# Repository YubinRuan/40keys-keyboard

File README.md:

# 40keys-keyboard
The PCB of 40keys-keyboard made by KICAD

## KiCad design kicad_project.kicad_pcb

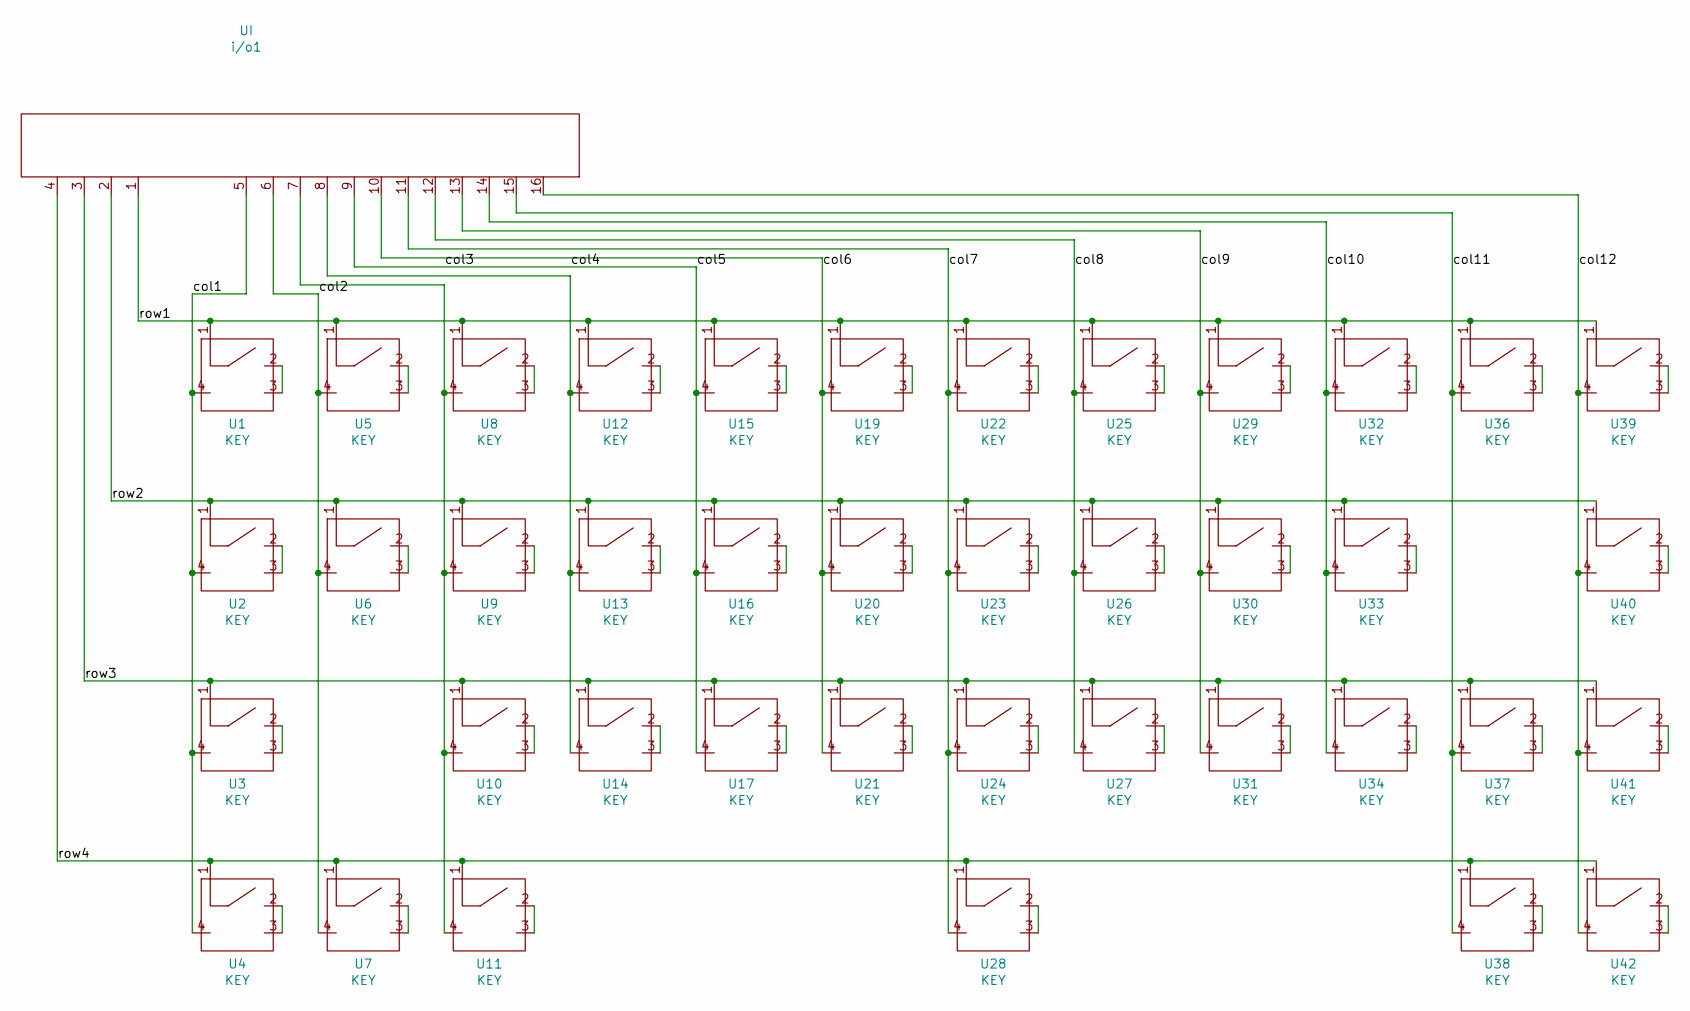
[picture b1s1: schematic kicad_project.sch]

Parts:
U1, U2, U3, U4, U5, U6, U7, U8, U9, U10, U11, U12, U13, U14, U15, U16, U17, U19, U20, U21, U22, U23, U24, U25, U26, U27, U28, U29, U30, U31, U32, U33, U34, U36, U37, U38, U39, U40, U41, U42: KEY; MX1As
i/o1: UI; ioport

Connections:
/col1: U1.4, U2.4, U3.4, U4.4, i/o1.5
/col2: U5.4, U6.4, U7.4, i/o1.6
/col3: U15.4, U16.4, U17.4, i/o1.9
/col6: U19.4, U20.4, U21.4, i/o1.10
/col7: U22.4, U23.4, U24.4, U28.4, i/o1.11
/col8: U25.4, U26.4, U27.4, i/o1.12
/col9: U29.4, U30.4, U31.4, i/o1.13
/col10: U32.4, U33.4, U34.4, i/o1.14
/col11: U36.4, U37.4, U38.4, i/o1.15
/col12: U39.4, U40.4, U41.4, U42.4, i/o1.16
/row1: U1.1, U5.1, U8.1, U12.1, U15.1, U19.1, U22.1, U25.1, U29.1, U32.1, U36.1, U39.1, i/o1.1
/row2: U2.1, U6.1, U9.1, U13.1, U16.1, U20.1, U23.1, U26.1, U30.1, U33.1, U40.1, i/o1.2
/row3: U3.1, U10.1, U14.1, U17.1, U21.1, U24.1, U27.1, U31.1, U34.1, U37.1, U41.1, i/o1.3
/row4: U4.1, U7.1, U11.1, U28.1, U38.1, U42.1, i/o1.4
unnamed: U1.2, U1.3
unnamed: U2.2, U2.3
unnamed: U3.2, U3.3
unnamed: U4.2, U4.3
unnamed: U5.2, U5.3
unnamed: U6.2, U6.3
unnamed: U7.2, U7.3
unnamed: U8.2, U8.3
unnamed: U9.2, U9.3
unnamed: U10.2, U10.3
unnamed: U8.4, U9.4, U10.4, U11.4, i/o1.7
unnamed: U11.2, U11.3
unnamed: U12.2, U12.3
unnamed: U12.4, U13.4, U14.4, i/o1.8
unnamed: U13.2, U13.3
unnamed: U14.2, U14.3
unnamed: U15.2, U15.3
unnamed: U16.2, U16.3
unnamed: U17.2, U17.3
unnamed: U19.2, U19.3
unnamed: U20.2, U20.3
unnamed: U21.2, U21.3
unnamed: U22.2, U22.3
unnamed: U23.2, U23.3
unnamed: U24.2, U24.3
unnamed: U25.2, U25.3
unnamed: U26.2, U26.3
unnamed: U27.2, U27.3
unnamed: U28.2, U28.3
unnamed: U29.2, U29.3
unnamed: U30.2, U30.3
unnamed: U31.2, U31.3
unnamed: U32.2, U32.3
unnamed: U33.2, U33.3
unnamed: U34.2, U34.3
unnamed: U36.2, U36.3
unnamed: U37.2, U37.3
unnamed: U38.2, U38.3
unnamed: U39.2, U39.3
unnamed: U40.2, U40.3
unnamed: U41.2, U41.3
unnamed: U42.2, U42.3

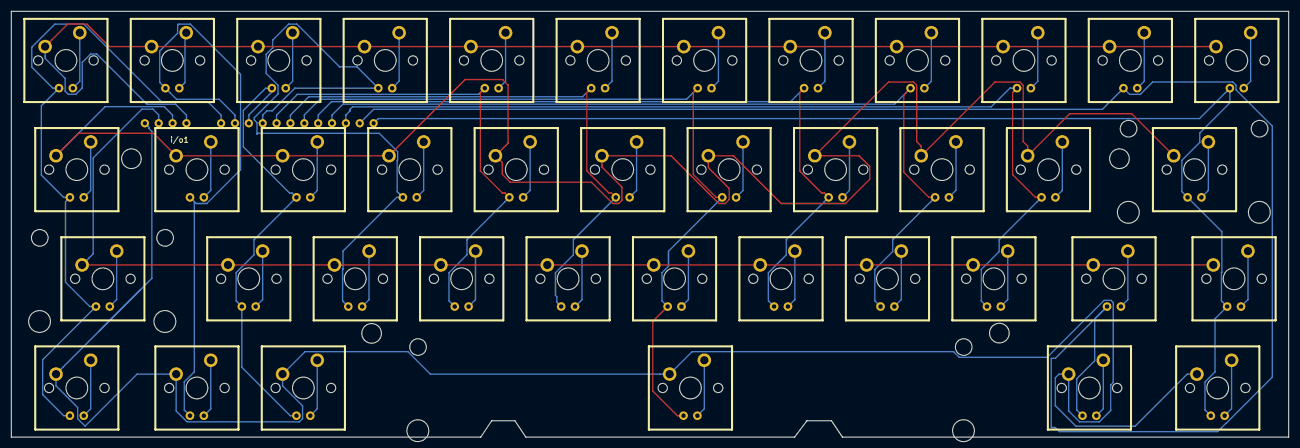
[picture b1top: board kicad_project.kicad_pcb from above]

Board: 2 copper layers, 234.0 x 78.0 mm, 41 parts (0 on the bottom side), 56 nets.

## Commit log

2019-03-22 40keys-keyboard
